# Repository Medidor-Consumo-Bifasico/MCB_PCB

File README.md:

# Medidor-Consumo-Electrico-Bifasico
Autor: avbazurt@espol.edu.ec

## Licensing information

## Requirements:
- Sensor PZE004T-100A
- ESP32-38pines

## Modo Monofasico:

## Modo Bifasico:

## Modo Trifasico:

## Mod de Hardware para usar con 3v3:

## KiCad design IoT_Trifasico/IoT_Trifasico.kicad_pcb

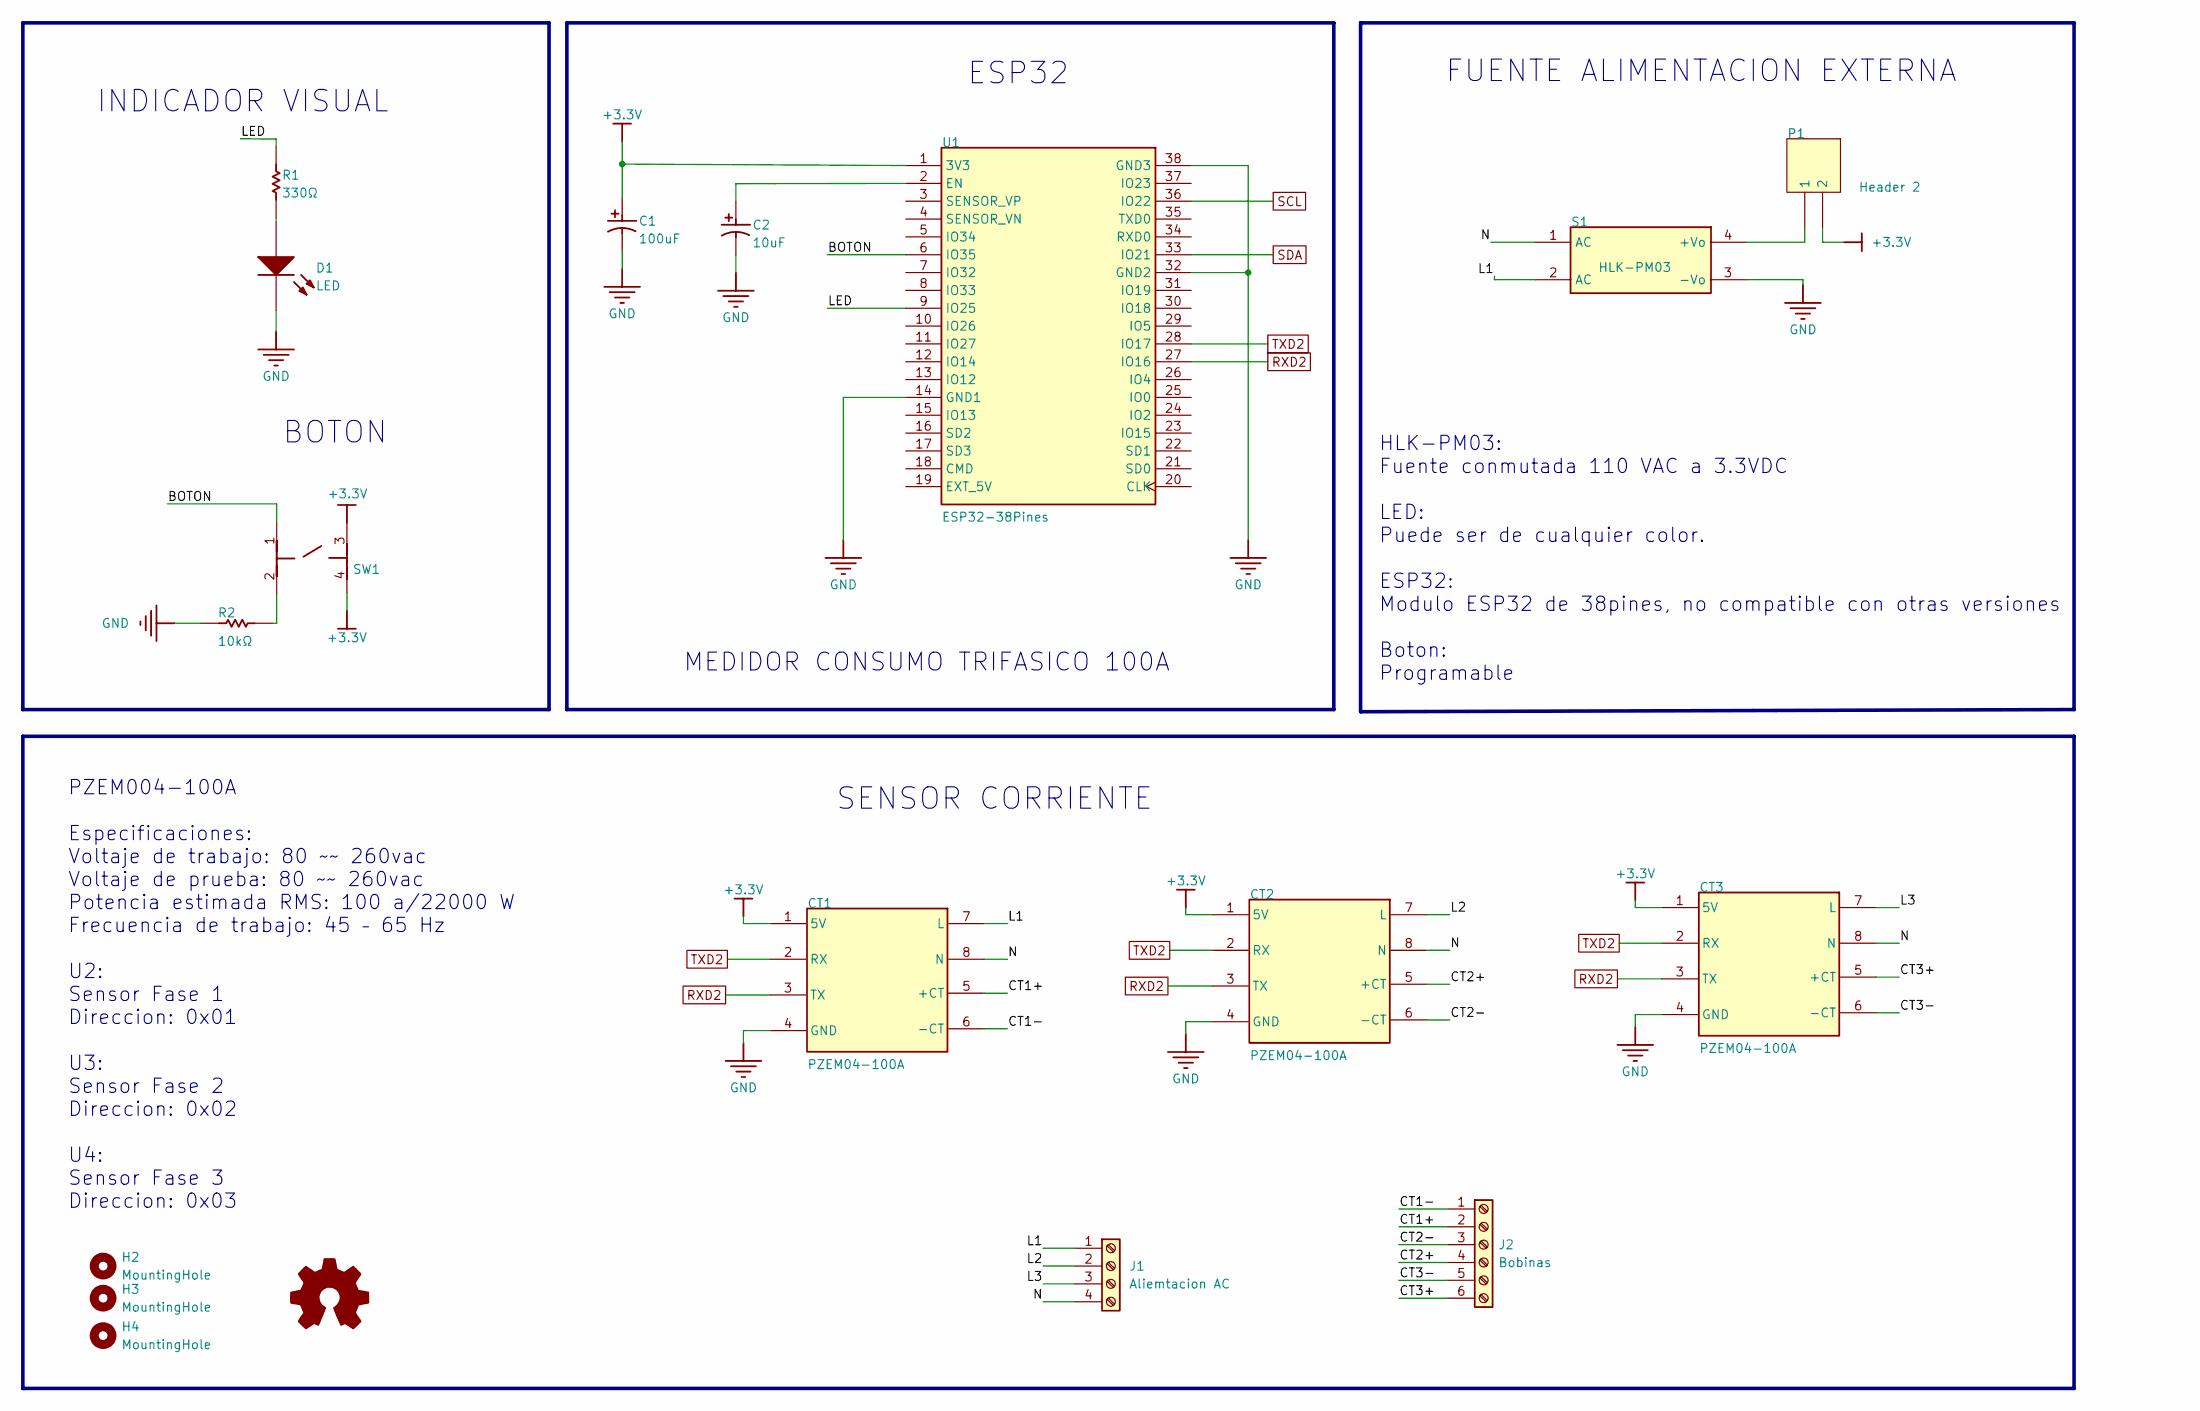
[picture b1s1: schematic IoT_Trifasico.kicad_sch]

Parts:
C1: 100uF; CP_Radial_D6.3mm_P2.50mm
C2: 10uF; CP_Radial_D5.0mm_P2.50mm
CT1, CT2, CT3: PZEM04-100A
D1: LED; LED_D5.0mm
H2, H3, H4: MountingHole; MountingHole_3.2mm_M3_DIN965_Pad
J1: Aliemtacion AC; TerminalBlock_bornier-4_P5.08mm
J2: Bobinas; TerminalBlock_bornier-6_P5.08mm
P1: Header 2; PinHeader_1x02_P2.54mm_Vertical
R1: 330Ω; R_Axial_DIN0207_L6.3mm_D2.5mm_P10.16mm_Horizontal
R2: 10kΩ; R_Axial_DIN0207_L6.3mm_D2.5mm_P10.16mm_Horizontal
S1: HLK-PM03; CONV_HLK-PM03
SW1: Button; SW_PUSH_6mm_H4.3mm
U1: ESP32-38Pines; MODULE_ESP32-DEVKITC-32D

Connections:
+3.3V: C1.1, CT1.1 (5V), CT2.1 (5V), CT3.1 (5V), P1.2, SW1.3, SW1.4, U1.1 (3V3)
/BOTON: SW1.1, U1.6 (IO35)
/CT1+: CT1.5 (+CT), J2.2
/CT1-: CT1.6 (-CT), J2.1
/CT2+: CT2.5 (+CT), J2.4
/CT2-: CT2.6 (-CT), J2.3
/CT3+: CT3.5 (+CT), J2.6
/CT3-: CT3.6 (-CT), J2.5
/L1: CT1.7 (L), J1.1, S1.2 (AC)
/L2: CT2.7 (L), J1.2
/L3: CT3.7 (L), J1.3
/LED: R1.2, U1.9 (IO25)
/N: CT1.8 (N), CT2.8 (N), CT3.8 (N), J1.4, S1.1 (AC)
GND: C1.2, C2.2, CT1.4 (GND), CT2.4 (GND), CT3.4 (GND), D1.2 (K), R2.1, S1.3 (-Vo), U1.14 (GND1), U1.32 (GND2), U1.38 (GND3)
unnamed: C2.1, U1.2 (EN)
unnamed: D1.1 (A), R1.1
unnamed: R2.2, SW1.2
unnamed: P1.1, S1.4 (+Vo)
RXD2: CT1.3 (TX), CT2.3 (TX), CT3.3 (TX), U1.27 (IO16)
SCL: U1.36 (IO22)
SDA: U1.33 (IO21)
TXD2: CT1.2 (RX), CT2.2 (RX), CT3.2 (RX), U1.28 (IO17)

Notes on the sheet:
BOTON
HLK-PM03: Fuente conmutada 110 VAC a 3.3VDC LED: Puede ser de cualquier color. ESP32: Modulo ESP32 de 38pines, no compatible con otras versiones Boton: Programable
INDICADOR VISUAL
PZEM004-100A Especificaciones: Voltaje de trabajo: 80 ~~ 260vac Voltaje de prueba: 80 ~~ 260vac Potencia estimada RMS: 100 a/22000 W Frecuencia de trabajo: 45 – 65 Hz U2: Sensor Fase 1 Direccion: 0x01 U3: Sensor Fase 2 Direccion: 0x02 U4: Sensor Fase 3 Direccion: 0x03
ESP32
SENSOR CORRIENTE
MEDIDOR CONSUMO TRIFASICO 100A
FUENTE ALIMENTACION EXTERNA

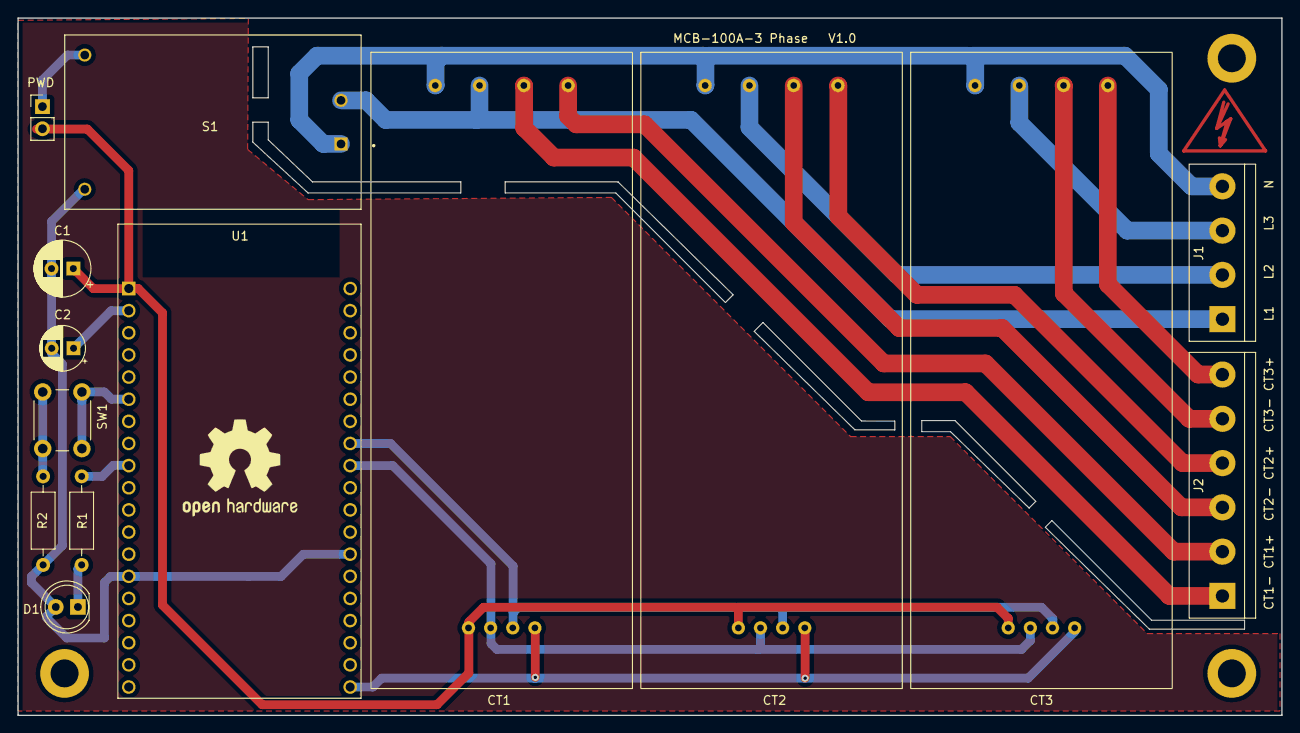
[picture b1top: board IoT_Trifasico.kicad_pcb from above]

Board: 2 copper layers, 145.0 x 80.0 mm, 17 parts (0 on the bottom side), 20 nets.

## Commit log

2021-12-01 Add Open Source Licenses
2023-01-03 Add a KiCAD Version in Three Phase Version
2023-01-03 add gitignore
2023-01-22 feat!: Added firmware & test succesfull with board
2023-01-22 docs: add link to hw mod and trifasic link to repo
